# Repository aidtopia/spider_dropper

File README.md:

# Stupidly Simply Spider Dropper

by Adrian McCarthy

A mechanism to "drop" a spider (or other lightweight prop) for Halloween fun.

## Overview

There are several versions of spider droppers out there.  Most require a microcontroller (like an Arduino Uno) and two actuators (for example, a motor to spool up the spider and a servo or solenoid to initiate the drop).  There are single-motor versions, but they require a reversing motor (which doesn't "drop" the spider so much as lower it) and a motor controller.

There's also at least one commercial "dropping spider" available at Halloween stores and party stores.  Those put the mechanism in the body of a comically unrealistic spider.

Although I enjoy programming and more complex projects, I wanted to make a spider dropper that required fewer parts (a.k.a. cheaper) and would be accessible to haunters who aren't interested in electronics, microcontrollers, and programming.

So I came up with the Stupidly Simple Spider Dropper.

("Stupidly Simple" refers to the design of the mechanism, not the haunters who use them.  The name is inspired by the KISS principle:  Keep It Simple, Stupid.)

There are three configurations:

1. Stupidly Simple Spider Dropper AC
2. Stupidly Simple Spider Dropper DC
3. Stupidly Simple Spider Dropper DC with the Slightly Smarter upgrade.

In the `docs` subfolder, you'll find the [Assembly Instructions](docs/assembly.md) as well as the [User Guide](docs/user_guide.md).

The `notes` subfolder is a hodgepodge of design ideas and information.

The `parts` subfolder has the OpenSCAD files that generate the 3D-printable parts (and some tools to help assemble them).  It also has a spreadsheet of what parts are needed, as well as links to specific items that I've used and some approximate pricing information.

The `schematics` subfolder has the KiCad files for the Slightly Smarter circuit.

## History

I'm a member of the Northern California Haunters Group.  We meet up several times a year to build Halloween props.  During a brainstorming session for the following year's Make & Take calendar, a fellow haunter suggested spider droppers.

There are several such projects online, but I think her suggestion may have been inspired specifically by [Arduino Dropping Spider Halloween Widget 62](https://www.youtube.com/watch?v=s5qQ0CaRchc) on the NYC CNC YouTube channel.  It's a neat project that has a mechanism using two servo motors (requiring modifications to one of them), an Arduino, and a ultrasonic distance sensor.  The immediate reaction from others in the group was that it was too ambitious to make in a few hours on a Saturday.  And that was probably true.

But it got me wondering whether there might a simpler way to achieve the same effect.  What if I could devise a 3D-printable mechanism that required only one motor to drive the drop and the reset?  Could it be done without a microcontroller?  Would a continuous drop-and-reset cycle provide creepy ambiance?

I had some "reindeer" motors left over from a previous project.  These are synchronous motors geared down to 6 RPM in a weather-resistant housing.  They're very light duty, but a toy spider isn't very heavy.  If I could base the cycle around one revolution of the motor, that would repeat every 10 seconds, which felt like a good pace.  My hope was that the dropper would be simple and inexpensive enough that a haunter could deploy a few of them in a spider-infested haunt to create creepy ambient motion.

The trick was to figure out how to have two different phases:  dropping and winding.  After trying to think up cam-driven mechanisms, I came up with the key idea that's powered this project:  A drive gear with a toothless section that allows the spool to spin freely.

I 3D-printed multiple prototypes trying to implement the idea.  The basic idea worked, but the spider bounced and spun around too much.  And the mechanism was prone to jamming when the bounce created enough slack to cause the string to get tangled in the mechanism.

I thought the solution was going to be to use elastic string to dampen the bounce from the sudden stop at the bottom of the drop.  I gave out a couple prototypes to fellow haunters to beta test in their displays.  The elastic string had made things worse.  The bounces were even more chaotic, and the spider's legs would get tangled in the string.  When it was hoisted back up, the spider would reach the top too soon and lock up the mechanism.  One of my beta testers painstakingly attached thread to the tips of each spider leg to keep the elastic string from getting between the legs.

On and off over the next couple years, I iterated on the design.  Elastic string was out.  Regular string (like kite string) was also problematic: The tension in the braid makes the spider want to spin like an ice skater, and, over time, it gets stretched out.  A big breakthrough was using monofilament (fishing line).  With a better spool design, monofilament is much less prone to tangling.

I switched to an open framework base plate because I thought it would look cool and be easier to experiment.  The unexpected benefit was that the open base plate doesn't amplify the motor noise.  The original slab design resonated with the motor vibrations, making it significantly louder.

I added skate bearings to the spool to reduce friction and avoid wear of the plastic parts.  This too had an unexpected (and more important) effect:  The additional rotational inertia of the bearings causes the spider to drop more smoothly, which looked better and further reduced problematic bouncing.

At some point, another Norcal haunter mentioned that he would be more interested in a DC version than one that uses an AC reindeer motor.  I searched around and found the JGY-370 motors, which are available with gear reduction to 6 RPM, just like the reindeer motors.  I made the base plate accommodate both styles of motor mount, but that still required two versions of the gears and spools due to differences in the shaft height and diameter.  I factored out those differences by creating the shaft adapaters which allow the rest of the mechanism to be motor-agnostic.

Despite all the progress, I grew bored with the project.  The continuous operation just wasn't as interesting as a drop triggered by the presence of the victim.

Around this time, I was playing around with mini PIR motion sensors.  PIR motion sensors generally aren't the right solution for triggering a startle effect because they're sensitive over a large area.  Haunters often try to control the field of view by recessing the sensors in a bit of PVC pipe, which helps but can be bulky.  And older sensors generally require a microcontroller to deal with "settling time" and "debouncing."  But these newer PIR sensors have a built-in microcontroller that handles those details.  These were small enough to fit into a discreet 3D-printed housing to control the detection zone.  In fact, I'd already designed such a housing.  I had even figured out how to reduce false triggers from distant motion.  They could be powered with 12 volts, the same voltage as the DC motors.  And they were inexpensive.

With what I'd learned about these newer PIR motion sensors, I realized I could start the DC motor turning with a simple circuit.  The only trick would be to turn the motor off just before the spider was about to drop.  I was vaguely aware of the "park" feature in windshield wiper motors, so I studied how those worked.  That was the last puzzle piece in the design of the Slightly Smarter upgrade.

And that inspired me to further refine the design until I had a kit design I felt good enough to share with other.

## Thanks To

Lynn for proposing a spider dropper Make & Take all those years ago.

CNC NYC for their inspiring spider dropper project.

Rex for teaching me enough about electronics to be dangerous, for opening my eyes to 3D printing and OpenSCAD, and for coming along on the journey from learning KiCad to making a custom PCB.

Ralph, Gigi, Mike, and Phyllis for beta testing and feedback.  Ralph and Gigi also helped me keep my mind open to mechanical solutions.  Mike for inspiring deeper exploration of sensors for triggering props.

DJ and Ernie who stress tested the first Slightly Smarter Spider Dropper in a real-life haunt during Halloween.

Mendora, Britta, and Glen for showing me that there is enough demand for the Stupidly Simple Spider Dropper to keep me motivated.

Jeff for helping out our fellow haunters with their soldering skills.

Suzanne for always reminding me that the techie projects need the crafty bits, too.

Kristi and Scott for hosting the (first?) Norcal Haunters Spider Dropper Make & Take.

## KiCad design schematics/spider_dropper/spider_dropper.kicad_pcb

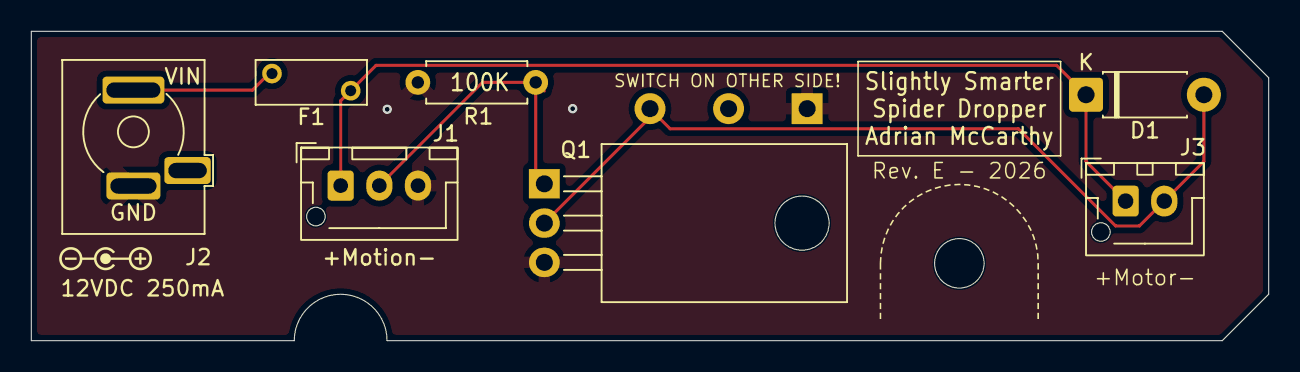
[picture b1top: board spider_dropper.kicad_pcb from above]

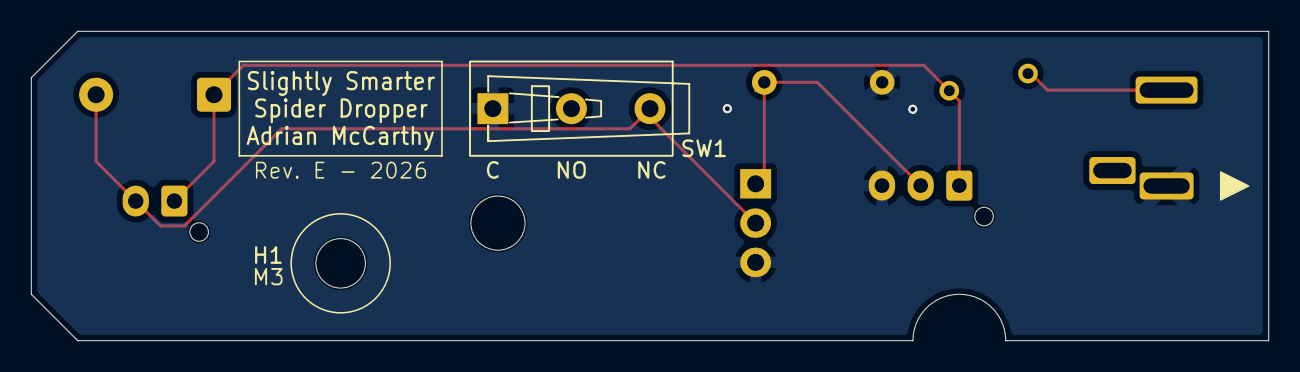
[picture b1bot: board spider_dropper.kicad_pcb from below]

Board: 2 copper layers, 80.0 x 20.0 mm, 10 parts (2 on the bottom side), 5 nets.

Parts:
D1: 1N4001; D_DO-41_SOD81_P7.62mm_Horizontal
F1: PTC 250mA; Fuse_BelFuse_0ZRC_L7.4mm_W3.1mm
G1: PolarityCenterPositive; PolarityCenterPositive_6x1.5mm_Silkscreen
H1: M3; MountingHole_3.2mm_M3
J1: JST_XH_3; JST_XH_B3B-XH-AM_1x03_P2.50mm_Vertical
J2: PJ-044AH; BarrelJack_SameSky(CUI)_PJ-044AH
J3: JST_XH_2; JST_XH_B2B-XH-AM_1x02_P2.50mm_Vertical
Q1: IRLZ34N; TO-220-3_Horizontal_TabDown
R1: 100K; R_Axial_DIN0207_L6.3mm_D2.5mm_P7.62mm_Horizontal
SW1: ZX40E20C01; SW_SPDT_THT_ZX_Microswitch_P5.08mm

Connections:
+12V: F1.1, J2.1
/MOTION: J1.2, Q1.1 (G), R1.1
/MOTOR+: D1.1 (K), F1.2, J1.1, J3.1
/MOTOR-: D1.2 (A), J3.2, Q1.2 (D), SW1.3 (A)
GND: J1.3, J2.2, Q1.3 (S), R1.2, SW1.1 (B)

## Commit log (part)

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2024-11-29 Setting up repot with a .gitignore.
2024-11-29 Capture the current schematics in the new repot.
2024-11-29 Bringing OpenSCAD sources in from another repo.
2024-11-30 Re-oriented and re-position the PCB and cradle.
    Also gave each printed part a unique color in preview.
    Rev A boards ordered from this commit.
2024-12-01 Carved space for the limit switch out of the drive gear.
    Instead of moving the gear and spool outwards, I thinned out a channel
    in the drive gear to accommodate the natural height of the limit switch.
2024-12-05 Started writing assembly instructions in the README.md.
2024-12-10 Made adjustements to the cradle.
    With the Rev A PCBs in hand, I discovered that the screw heads holding
    the cradle would interfere with the power and motor connectors, so I
    moved them inward.
    I also extended the "index" pin on the cradle up through the base plate
    to ensure proper orientation of the PCB.
    The cradle is too flimsy. I plan to address that soon.
2024-12-10 JGY motor shaft uses M3 not M4 hub screw.
    This was probably a copy-modify-paste error from the deer motor,
    long, long ago.
2024-12-10 Removed (most of) the instructions from the SCAD file.
2024-12-11 Applied more tweaks to the cradle.
    Tried to stiffen it up and improve the mounts.
2024-12-15 Experimenting with a better cradle and a limit switch mounting block.
    The cradle was twising easily, and, since it's only screwed in from
    one side, the other long edge was drooping. This is an attempt to
    beef-up the cradle to prevent that.
    I got feedback that having the limit switch soldered directly to the
    PCB might cause strain on the PCB that could reduce its lifetime, so I
    also started designing a mounting block to hold the limit switch. The
2024-12-15 Updated the parts spreadsheet.
2024-12-15 The .lck file should not have been checked in.
    I believe those are temporary lock files used by KiCad.
2024-12-22 Updated PCB layout (now Rev. B) for more clearance around connectors.
    The motion sensor header was within the margin, but the motion sensor
    itself would run into the edge of the deeper cradle. I centered it
    on the short axis and aligned it with the index post on the long axis.
    This should enable the cradle to have some supports for the sensor
    module or a cable that connects to it.
2024-12-22 Made the PCB cradle a little shorter.
    It should still be comfortably taller than the connectors, while
    reducing the conflict between the motion sensor and the wall of
    the cradle.
    To ensure good slicing results, I fudged the height of the holes for
    power and motor wires passing through the wall of the cradle.
2024-12-23 Reduced the depth of the nut pockets in the cradle to ease assembly.
    Also tweaked the power connector hole for a stronger print.
2024-12-24 More PCB layout tweaks to ease assembly.
    Power connector is closer to cradle wall so that there's enough room
    for a fat plug.
    Fuse and TIP120 are in a little more from the edges.
    Resistors and BJT are shifted to space out the pads for easier
    soldering.
2025-01-12 Switched the JST XH footprint to one with hole for "boss".
    The boss is for alignment and possibly additional support. This
    footprint is compatible with the connector that doesn't have a boss.
2025-08-13 Tried to do circuit simulation in KiCad. Not working yet.
    The Spice models are from manufacturer OnSemi's website.
2025-08-13 Removed the unused switch mounting block from the SCAD design.
2025-08-15 Modified one dimension to improve motor mount strength.
    deer_base_d is the diameter of the cutout to accommodate the raised
    area on the face of a reindeer motor. Making this slightly smaller
    allowed more "meat" around the mounting holes for a JGY motor without
    compromising the fit for the reindeer motor.
2025-08-15 Added current-limiting resistor to base of Q2.
    With the thermal camera, I happened to notice that Q1 was heating up
    more than I expected. When on, it was passing almost 11mA. Within
    spec, but way more than necessary to turn on Q2. Added a current
    limited resistor to the base of Q2 dropped the current (and power)
    through Q1 to less than 1mA.
    Made additional layout tweaks to PCB and updated markings to Rev C.
2025-08-28 Started a re-do of the 3D-printed parts.
2025-08-29 Checkpoint on version 2 parts.
    Base plate is feature complete.
2025-08-29 Checkpoint latest version of Rev D schematic and PCB.
2025-08-31 Added notes about whether the MOSFET needs a heatsink.
2025-08-31 Needed a tighter fit on the splines.
2025-08-31 Got 3D models for the JST connectors to appear in rendering.
    I'm using the KiCad-provided models for the connectors without the
    extra alignment nubs. But I didn't want to switch the footprint
    because I want the PCB to have the holes for those nubs.
2025-08-31 Removed unnecessary parameter from spline_shape. YAGNI.
2025-08-31 Fixed size of PCB mounting tab and added a nut pocket.
2025-08-31 Updated comments and started reconstructing the assembly preview.
2025-08-31 Started updating and re-integrating the spool assembly.
    Also fixed plate_l to accomodate gap for the alternate string guide.
2025-09-02 I think I'm ready to order Rev. D PCBs.
2025-09-03 Made the shaft adapter beefier; improved tie-off for string to spool.
    When the mechanism gets jammed up, the shaft adapter was failing a
    little easier than it should.
    The current way of securing the string to the spool works, but I have
    ideas for making it better.
2025-09-04 Made a spreadsheet to better understand the sizing contraints.
    The parameterization of the drop distance is very limited because the
    SCAD code doesn't currently adjust the tooth counts or gear ratios.
    Adjusting the diameter of the spool can only go so far until you hit
    a constraint.
2025-09-04 Improved tie-off for the string on the spool.
    This works well, but there's still room for improvement.
    Also computed the minimum tooth counts for the gears in preparation for
    improved parameterization. The computed values match the ones that
    have been hardcoded for a long time now.
2025-09-06 Added the spool guard and redesigned the axle.
2025-09-06 Continued tweaking the gear ratio spreadsheet.
2025-09-07 Added a cap screw to hold the drive, and adjusted the new axle.
    The cap screw kinda works when printing with 0.3mm layers, but it
    would work better at 0.2mm. It's essentially a 1/4"x20 bolt. In a
    pinch you can force in a tripod mounting screw.
    I'd gotten to a nice fit with a prototype axle, but when it was printed
    as part of the base plate, the shrinkage was different and thus the
    spool assembly didn't fit at all. After more experimentation, I dialed
2025-09-12 Another fix to shaft adapters (and cap screw).
    Recent changes prevented the shaft adapter from sliding all the way
    down to the JGY motor base, which meant the drive gear was too high
    and wouldn't depress the switch on the Slightly Smarter PCB.
    Fix was to make the cap screw diameter larger than the shaft diameter.
    To get good threads, the adapter and the cap screw require 0.2mm layers
    (or better). The rest of the parts can still be printed with 0.3mm.
2025-09-12 Changed PCB model to accept a limit for the switch position.
    This was helpful in debugging a clearance and dragging issue.
2025-09-15 Made more tweaks to the build plate.
    Added a pocket to hold the end of the PCB near the power connector. It
    has a drooping bridge and needs some sort of support.
    Turned off the spool guard experiment. It doesn't help.
    Tried again to make a tighter fitting axle. This works better, but the
    variation from print-to-print means it won't always be better.
2025-09-16 Ignore most images in the notes subdirectory.
2025-09-21 Several improvements.
    * Abandoned the ribbed axle and might a tight, strong one like before.
    * Added a module to generate text axles.
    * Added a bridge to capture the end of the PCB to reduce flexing.
    * Added a jig to hold the switch in position while soldering it.
    * Added a bearing pusher tool.
    * Used the KiCad-generated STL for visualizing the PCB.
2025-09-21 Small improvements for Rev. E.
    * Moved the connectors to make it easier to connect & disconnect.
    * Moved the diode in from the corner.
    * Added detail to the perimeter boundary (in User Drawings layer).
    * Added a triangular arrow to assist with alignment in assembly.
2025-09-21 Changed the diode footprint to a DO-41.
    The leads of the 1N4001 diodes I have barely fit into the holes for the
    default footprint. Datasheet suggests DO-41 is the correct package,
    and KiCad has a footprint for that with the same spacing but larger
    holes.
2025-09-21 Had a discussion with ChatGPT about naming the next version.
2025-09-28 Switched to smaller, cheaper signal diode.
    The 1N4001 was overkill for the motor flyback. The 1N4148 is a common
    signal diode that fits the space a little better.
    Also nudged the connector for the motor controller to help my fat
    fingers access it.
2025-10-15 Reverted change to the diode. Back to 1N4001.
2026-04-30 Added Customizer option for thin square nuts (recommended).
2026-04-30 Fixed typo in osh_v_pcb.md.
2026-05-09 Customizer now allows heat-set inserts for shaft adapter set screws.
2026-05-10 Updated after adding barrel connector model to library.
2026-05-26 Added MOSFET pin bender tool.
2026-05-26 Made shaft adapters widers and tweaked dimensions for heat-set inserts.
2026-05-26 Added draft of assembly instructions and tweaked the user guide.
2026-05-27 Improved the PCB model visualization in OpenSCAD.
    Added batch file that generates two STL models from the KiCAD PCB
    layout. The two are tinted different colors and combined to make a
    more realistic model.
    Note the switch model in KiCAD has a bigger lever than the part
    specified, so it may not look like it aligns correctly.
2026-05-27 Added pin bender to main SCAD file and tweaked print layout of parts.
2026-05-27 Added PIR housing to spider dropper project.
2026-05-30 Added model of JGY motor for visualization.
2026-05-30 Updated gear_ratios spreadsheet.
2026-06-03 Started editing the assembly.md and adding illustrations.
2026-06-03 Improved visualizations by adding motor models and animation.
    The code for the motor models is hacky, but good enough to see what's
    going on. The animation turns the motor shaft, shaft adapter, drive
    gear, hub screw, and spool. The spool even rapidly unwinds for the
    drop.
2026-06-03 Added print_jobs.txt.
    This shows how parts can be groups for printing.
2026-06-04 Added deer_motor_outline.png.
    I traced the lid of the deer motor housing to get better measurements.
    This is a flatbed scan of that tracing for reference.
2026-06-04 Added video/demo.py to make illustrative videos.
    This is a crude Python script to generate frames using OpenSCAD's
    command line interface and then to stitch them together with ffmpeg.
    OpenSCAD's own animation generator still doesn't work from the command
    line on Windows, despite somebody accepting my pull request a few
    years ago. So the script generates the frames one at a time.
2026-06-05 Added bearings to visualization of the spool assembly.
2026-06-05 Applied fix to make gears mesh better in preview.
2026-06-10 Did more editing of assembly instructions; started adding diagrams.
2026-06-17 Did more editing of assembly instructions.
2026-06-17 Corrected information about where to put the heat-shrink tubing.
    These are bits that are they to cushion the cable where strain relief
    is applied.
2026-06-21 Revised parts spreadsheet.
    Reflects new parts prices. Credits the Slightly Smarter model for the
    DC barrel pigtail that would have come with the basic DC model. Fixes
    some formatting.
2026-06-21 Deleted the old spider_dropper.scad file. Not going back.
    In a subsequent step, spider_dropper2.scad will will the 2.
